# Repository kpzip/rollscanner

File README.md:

# rollscanner
88-Note Piano Roll scanner

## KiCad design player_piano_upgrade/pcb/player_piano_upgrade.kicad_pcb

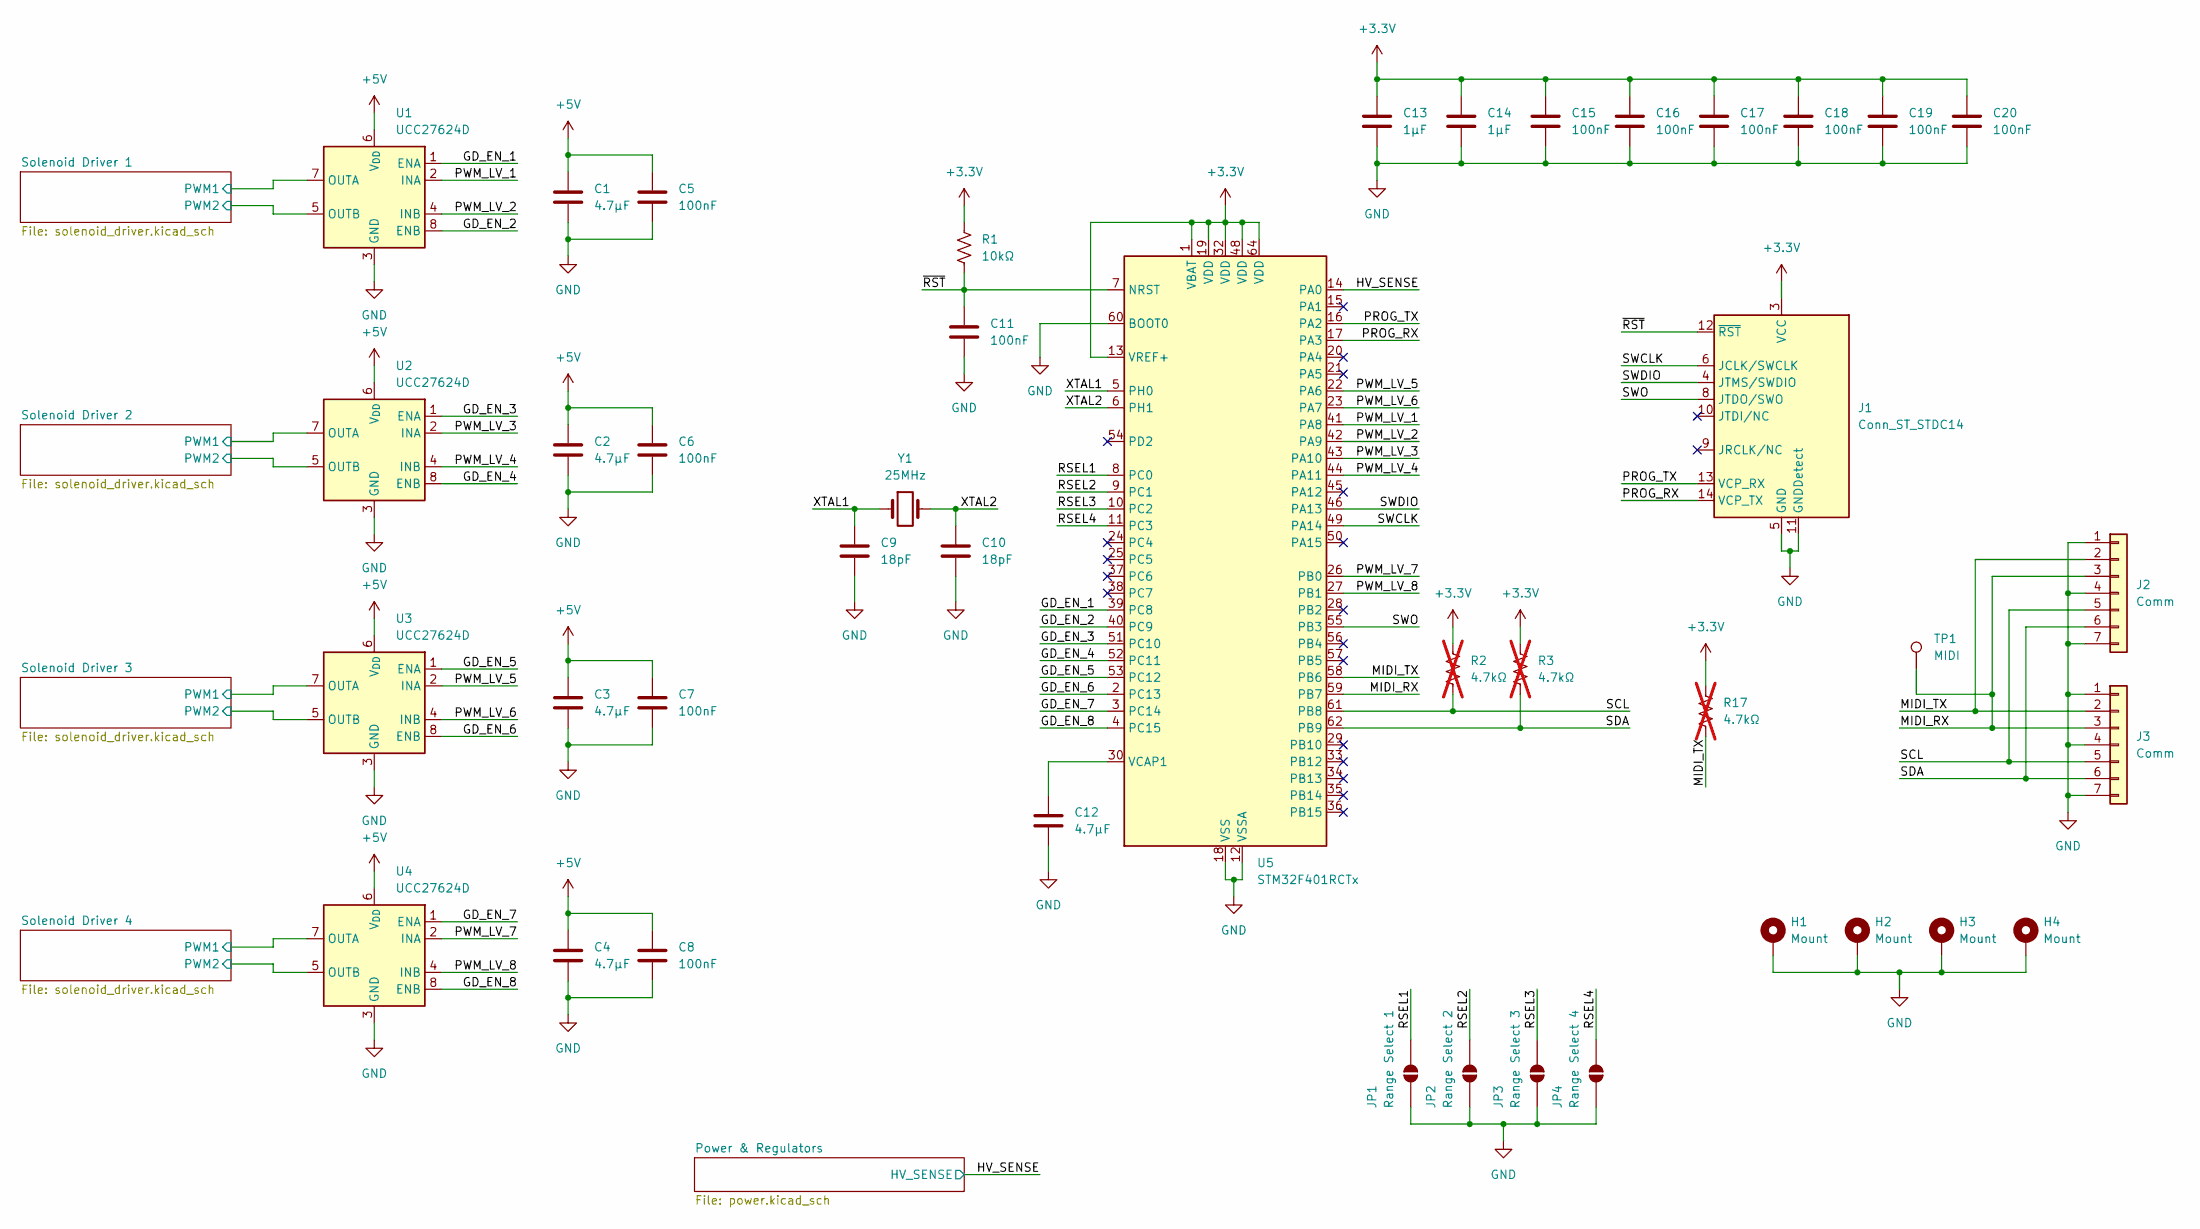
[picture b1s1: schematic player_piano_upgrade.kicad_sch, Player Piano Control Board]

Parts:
C1, C2, C3, C4, C12: 4.7μF; C_1206_3216Metric; Manufacturer Part Number CL31B475KAHNNNE
C5, C6, C7, C8, C11, C15, C16, C17, C18, C19, C20: 100nF; C_1206_3216Metric; Manufacturer Part Number CL31B104KBCNNNC
C9, C10: 18pF; C_0402_1005Metric; Manufacturer Part Number GJM1555C1H180GB01D
C13, C14: 1μF; C_1206_3216Metric; Manufacturer Part Number CL31B105KCHNNNE
H1, H2, H3, H4: Mount; MountingHole_3.2mm_M3_DIN965_Pad
J1: Conn_ST_STDC14; PinHeader_2x07_P1.27mm_Vertical_SMD; Manufacturer Part Number FTSH-107-01-L-DV-K
J2, J3: Comm; JST_PH_B7B-PH-K_1x07_P2.00mm_Vertical; Manufacturer Part Number B7B-PH-K-S
JP1: Range Select 1; SolderJumper-2_P1.3mm_Open_RoundedPad1.0x1.5mm
JP2: Range Select 2; SolderJumper-2_P1.3mm_Open_RoundedPad1.0x1.5mm
JP3: Range Select 3; SolderJumper-2_P1.3mm_Open_RoundedPad1.0x1.5mm
JP4: Range Select 4; SolderJumper-2_P1.3mm_Open_RoundedPad1.0x1.5mm
R1: 10kΩ; R_1206_3216Metric; Manufacturer Part Number FRC1206F1002TS
R2, R3, R17: 4.7kΩ; R_1206_3216Metric; Manufacturer Part Number FRC1206F4701TS; not fitted
TP1: MIDI; TestPoint_Pad_D1.0mm
U1, U2, U3, U4: UCC27624D; SOIC-8_3.9x4.9mm_P1.27mm; Manufacturer Part Number UCC27624DR
U5: STM32F401RCTx; LQFP-64_10x10mm_P0.5mm; Manufacturer Part Number STM32F401RCT6
Y1: 25MHz; Crystal_SMD_HC49-SD; Manufacturer Part Number ECS-250-18-5PX-F-TR

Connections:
+3.3V: C13.1, C14.1, C15.1, C16.1, C17.1, C18.1, C19.1, C20.1, J1.3 (VCC), R1.1, R2.1, R3.1, R17.1, U5.1 (VBAT), U5.13 (VREF+), U5.19 (VDD), U5.32 (VDD), U5.48 (VDD), U5.64 (VDD); also elsewhere on the board
+5V: C1.1, C2.1, C3.1, C4.1, C5.1, C6.1, C7.1, C8.1, U1.6 (V_{DD}), U2.6 (V_{DD}), U3.6 (V_{DD}), U4.6 (V_{DD}); also elsewhere on the board
/GD_EN_1: U1.1 (ENA), U5.39 (PC8)
/GD_EN_2: U1.8 (ENB), U5.40 (PC9)
/GD_EN_3: U2.1 (ENA), U5.51 (PC10)
/GD_EN_4: U2.8 (ENB), U5.52 (PC11)
/GD_EN_5: U3.1 (ENA), U5.53 (PC12)
/GD_EN_6: U3.8 (ENB), U5.2 (PC13)
/GD_EN_7: U4.1 (ENA), U5.3 (PC14)
/GD_EN_8: U4.8 (ENB), U5.4 (PC15)
/HV_SENSE: U5.14 (PA0); also elsewhere on the board
/MIDI_RX: J2.3, J3.3, TP1.1 (1_1), U5.59 (PB7)
/MIDI_TX: J2.2, J3.2, R17.2, U5.58 (PB6)
/PROG_RX: J1.14 (VCP_TX), U5.17 (PA3)
/PROG_TX: J1.13 (VCP_RX), U5.16 (PA2)
/PWM_LV_1: U1.2 (INA), U5.41 (PA8)
/PWM_LV_2: U1.4 (INB), U5.42 (PA9)
/PWM_LV_3: U2.2 (INA), U5.43 (PA10)
/PWM_LV_4: U2.4 (INB), U5.44 (PA11)
/PWM_LV_5: U3.2 (INA), U5.22 (PA6)
/PWM_LV_6: U3.4 (INB), U5.23 (PA7)
/PWM_LV_7: U4.2 (INA), U5.26 (PB0)
/PWM_LV_8: U4.4 (INB), U5.27 (PB1)
/RSEL1: JP1.2 (B), U5.8 (PC0)
/RSEL2: JP2.2 (B), U5.9 (PC1)
/RSEL3: JP3.2 (B), U5.10 (PC2)
/RSEL4: JP4.2 (B), U5.11 (PC3)
/SCL: J2.5, J3.5, R2.2, U5.61 (PB8)
/SDA: J2.6, J3.6, R3.2, U5.62 (PB9)
/SWCLK: J1.6 (JCLK/SWCLK), U5.49 (PA14)
/SWDIO: J1.4 (JTMS/SWDIO), U5.46 (PA13)
/SWO: J1.8 (JTDO/SWO), U5.55 (PB3)
/Solenoid Driver 1/PWM1: U1.7 (OUTA); also elsewhere on the board
/Solenoid Driver 1/PWM2: U1.5 (OUTB); also elsewhere on the board
/Solenoid Driver 2/PWM1: U2.7 (OUTA); also elsewhere on the board
/Solenoid Driver 2/PWM2: U2.5 (OUTB); also elsewhere on the board
/Solenoid Driver 3/PWM1: U3.7 (OUTA); also elsewhere on the board
/Solenoid Driver 3/PWM2: U3.5 (OUTB); also elsewhere on the board
/Solenoid Driver 4/PWM1: U4.7 (OUTA); also elsewhere on the board
/Solenoid Driver 4/PWM2: U4.5 (OUTB); also elsewhere on the board
/XTAL1: C9.1, U5.5 (PH0), Y1.1
/XTAL2: C10.1, U5.6 (PH1), Y1.2
/~RST: C11.1, J1.12 (~RST), R1.2, U5.7 (NRST)
GND: C1.2, C2.2, C3.2, C4.2, C5.2, C6.2, C7.2, C8.2, C9.2, C10.2, C11.2, C12.2, C13.2, C14.2, C15.2, C16.2, C17.2, C18.2, C19.2, C20.2, H1.1 (1_1), H2.1 (1_1), H3.1 (1_1), H4.1 (1_1), J1.5 (GND), J1.7 (GND), J1.11 (GNDDetect), J2.1, J2.4, J2.7, J3.1, J3.4, J3.7, JP1.1 (A), JP2.1 (A), JP3.1 (A), JP4.1 (A), U1.3 (GND), U2.3 (GND), U3.3 (GND), U4.3 (GND), U5.12 (VSSA), U5.18 (VSS), U5.31 (VSS), U5.47 (VSS), U5.60 (BOOT0), U5.63 (VSS); also elsewhere on the board
unnamed: C12.1, U5.30 (VCAP1)

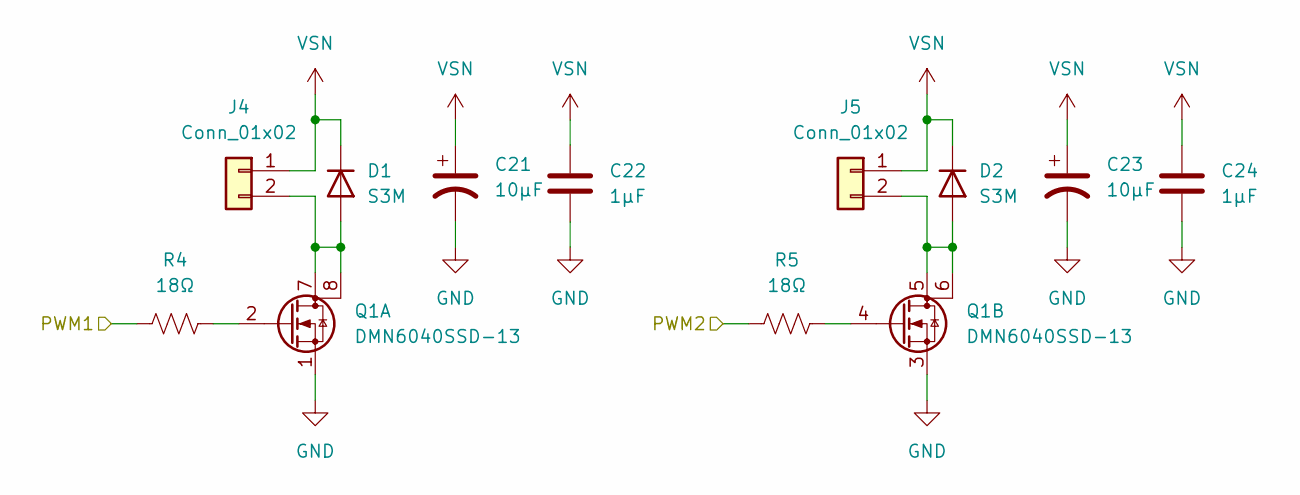
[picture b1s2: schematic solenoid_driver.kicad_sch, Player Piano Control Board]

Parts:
C21, C23: 10μF; CP_Elec_6.3x5.8; Manufacturer Part Number HBW100M1JTR-0606
C22, C24: 1μF; C_1206_3216Metric; Manufacturer Part Number CL31B105KCHNNNE
D1, D2: S3M; D_SMB; Manufacturer Part Number S3M
J4, J5: Conn_01x02; Molex_KK-254_AE-6410-02A_1x02_P2.54mm_Vertical; Manufacturer Part Number A2543WV-2P
Q1: DMN6040SSD-13; SOIC-8_3.9x4.9mm_P1.27mm; Manufacturer Part Number DMN6040SSD-13
R4, R5: 18Ω; R_1206_3216Metric; Manufacturer Part Number FRC1206F18R0TS

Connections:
/Solenoid Driver 1/PWM1: R4.1; also elsewhere on the board
/Solenoid Driver 1/PWM2: R5.1; also elsewhere on the board
GND: C21.2, C22.2, C23.2, C24.2, Q1.1 (S), Q1.3 (S); also elsewhere on the board
unnamed: D1.2 (A), J4.2, Q1.7 (D), Q1.8 (D)
unnamed: D2.2 (A), J5.2, Q1.5 (D), Q1.6 (D)
unnamed: Q1.2 (G), R4.2
unnamed: Q1.4 (G), R5.2
VSN: C21.1, C22.1, C23.1, C24.1, D1.1 (K), D2.1 (K), J4.1, J5.1; also elsewhere on the board

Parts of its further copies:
C25, C27, C29, C31, C33, C35: 10μF; CP_Elec_6.3x5.8; Manufacturer Part Number HBW100M1JTR-0606
C26, C28, C30, C32, C34, C36: 1μF; C_1206_3216Metric; Manufacturer Part Number CL31B105KCHNNNE
D3, D4, D5, D6, D7, D8: S3M; D_SMB; Manufacturer Part Number S3M
J6, J7, J8, J9, J10, J11: Conn_01x02; Molex_KK-254_AE-6410-02A_1x02_P2.54mm_Vertical; Manufacturer Part Number A2543WV-2P
Q2, Q3, Q4: DMN6040SSD-13; SOIC-8_3.9x4.9mm_P1.27mm; Manufacturer Part Number DMN6040SSD-13
R6, R7, R8, R9, R10, R11: 18Ω; R_1206_3216Metric; Manufacturer Part Number FRC1206F18R0TS

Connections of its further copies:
/Solenoid Driver 2/PWM1: R6.1; also elsewhere on the board
/Solenoid Driver 2/PWM2: R7.1; also elsewhere on the board
/Solenoid Driver 3/PWM1: R8.1; also elsewhere on the board
/Solenoid Driver 3/PWM2: R9.1; also elsewhere on the board
/Solenoid Driver 4/PWM1: R10.1; also elsewhere on the board
/Solenoid Driver 4/PWM2: R11.1; also elsewhere on the board
GND: C25.2, C26.2, C27.2, C28.2, C29.2, C30.2, C31.2, C32.2, C33.2, C34.2, C35.2, C36.2, Q2.1 (S), Q2.3 (S), Q3.1 (S), Q3.3 (S), Q4.1 (S), Q4.3 (S); also elsewhere on the board
unnamed: D3.2 (A), J6.2, Q2.7 (D), Q2.8 (D)
unnamed: D4.2 (A), J7.2, Q2.5 (D), Q2.6 (D)
unnamed: D5.2 (A), J8.2, Q3.7 (D), Q3.8 (D)
unnamed: D6.2 (A), J9.2, Q3.5 (D), Q3.6 (D)
unnamed: D7.2 (A), J10.2, Q4.7 (D), Q4.8 (D)
unnamed: D8.2 (A), J11.2, Q4.5 (D), Q4.6 (D)
unnamed: Q2.2 (G), R6.2
unnamed: Q2.4 (G), R7.2
unnamed: Q3.2 (G), R8.2
unnamed: Q3.4 (G), R9.2
unnamed: Q4.2 (G), R10.2
unnamed: Q4.4 (G), R11.2
VSN: C25.1, C26.1, C27.1, C28.1, C29.1, C30.1, C31.1, C32.1, C33.1, C34.1, C35.1, C36.1, D3.1 (K), D4.1 (K), D5.1 (K), D6.1 (K), D7.1 (K), D8.1 (K), J6.1, J7.1, J8.1, J9.1, J10.1, J11.1; also elsewhere on the board

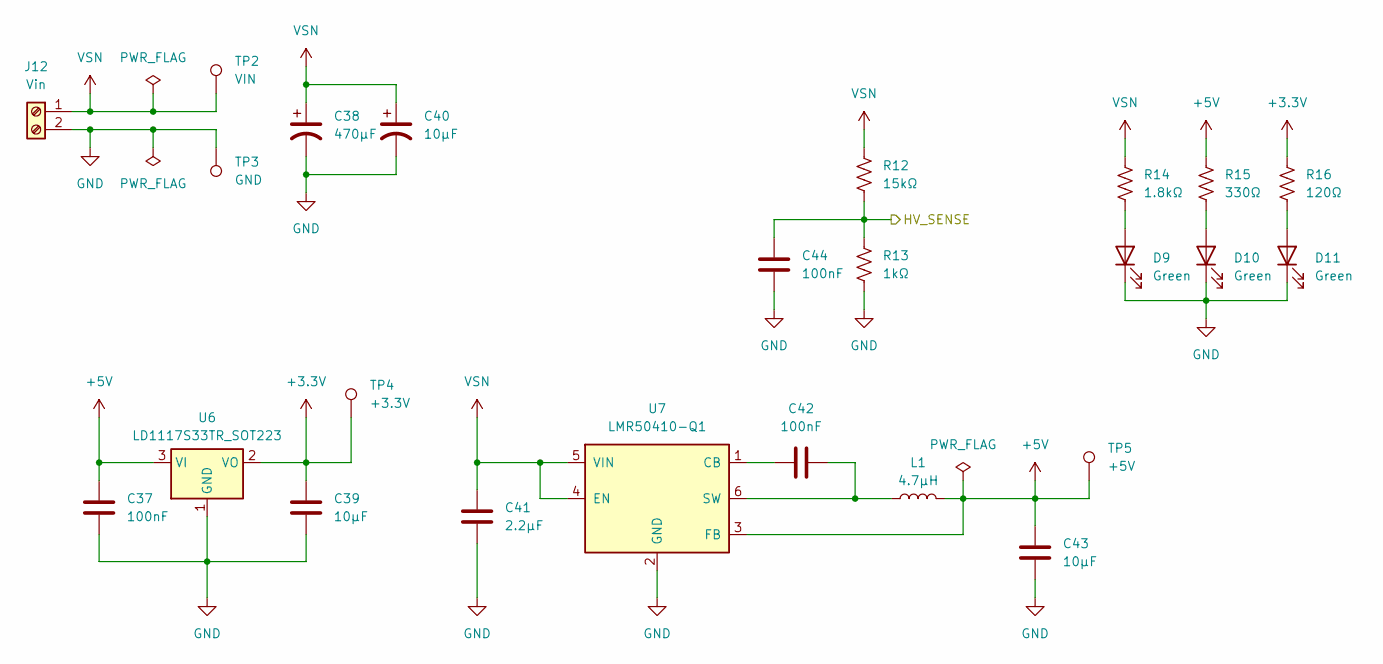
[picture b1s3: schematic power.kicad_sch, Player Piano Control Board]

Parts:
C37, C42, C44: 100nF; C_1206_3216Metric; Manufacturer Part Number CL31B104KBCNNNC
C38: 470μF; CP_Radial_D10.0mm_P5.00mm; Manufacturer Part Number 50PX470MEFC10X20
C39, C43: 10μF; C_1206_3216Metric; Manufacturer Part Number CL31A106MAHNNNE
C40: 10μF; CP_Elec_6.3x5.8; Manufacturer Part Number HBW100M1JTR-0606
C41: 2.2μF; C_1206_3216Metric; Manufacturer Part Number TCC1206X7R225K101HT
D9, D10, D11: Green; LED_D5.0mm; Manufacturer Part Number WP7113GD
J12: Vin; TerminalBlock_CUI_TB007-508-02_1x02_P5.08mm_Horizontal; Manufacturer Part Number WJ500V-5.08-2P
L1: 4.7μH; L_1008_2520Metric_Pad1.43x2.20mm_HandSolder; Manufacturer Part Number DFE252012P-4R7M=P2
R12: 15kΩ; R_1206_3216Metric; Manufacturer Part Number HRC1206F1502HNTN
R13: 1kΩ; R_1206_3216Metric; Manufacturer Part Number FRC1206J102 TS
R14: 1.8kΩ; R_1206_3216Metric; Manufacturer Part Number AC1206FR-7W1K8L
R15: 330Ω; R_1206_3216Metric; Manufacturer Part Number RMS12FT3300
R16: 120Ω; R_1206_3216Metric; Manufacturer Part Number FRC1206F1200TS
TP2: VIN; TestPoint_Pad_D1.0mm
TP3: GND; TestPoint_Pad_D2.0mm
TP4: +3.3V; TestPoint_Pad_D1.0mm
TP5: +5V; TestPoint_Pad_D1.0mm
U6: LD1117S33TR_SOT223; SOT-223-3_TabPin2; Manufacturer Part Number LD1117S33TR
U7: LMR50410-Q1; SOT-23-6; Manufacturer Part Number LMR50410Y5FQDBVRQ1

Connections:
+3.3V: C39.1, R16.1, TP4.1 (1_1), U6.2 (VO); also elsewhere on the board
+5V: C37.1, C43.1, L1.2, R15.1, TP5.1 (1_1), U6.3 (VI), U7.3 (FB); also elsewhere on the board
/HV_SENSE: C44.2, R12.2, R13.1; also elsewhere on the board
GND: C37.2, C38.2, C39.2, C40.2, C41.2, C43.2, C44.1, D9.1 (K), D10.1 (K), D11.1 (K), J12.2, R13.2, TP3.1 (1_1), U6.1 (GND), U7.2 (GND); also elsewhere on the board
unnamed: D9.2 (A), R14.2
unnamed: D10.2 (A), R15.2
unnamed: D11.2 (A), R16.2
unnamed: C42.1, U7.1 (CB)
unnamed: C42.2, L1.1, U7.6 (SW)
VSN: C38.1, C40.1, C41.1, J12.1, R12.1, R14.1, TP2.1 (1_1), U7.4 (EN), U7.5 (VIN); also elsewhere on the board

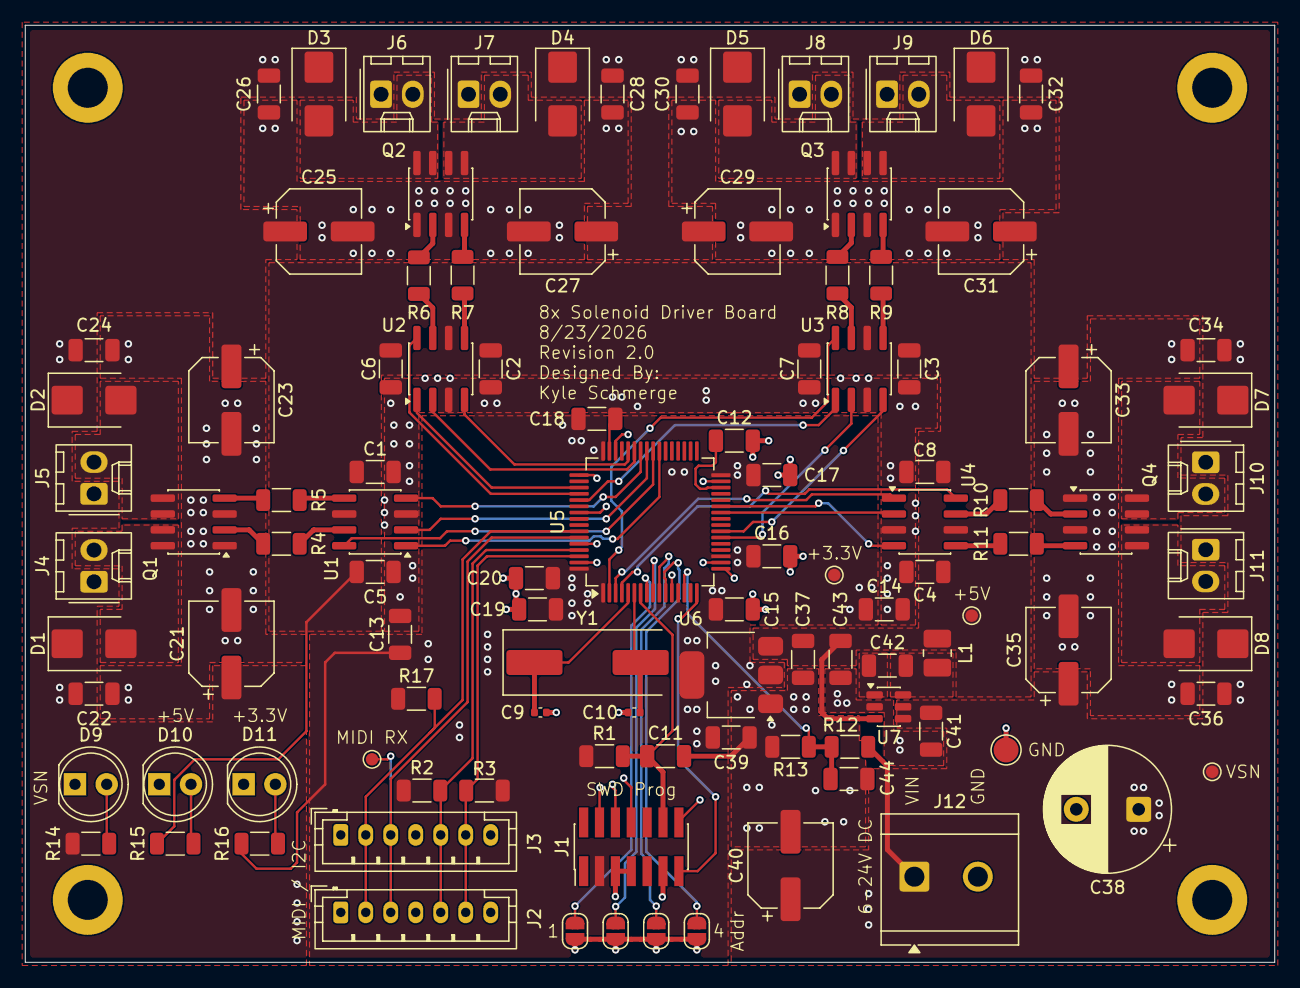
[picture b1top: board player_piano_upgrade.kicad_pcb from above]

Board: 4 copper layers, 100.0 x 75.0 mm, 110 parts (0 on the bottom side), 67 nets.

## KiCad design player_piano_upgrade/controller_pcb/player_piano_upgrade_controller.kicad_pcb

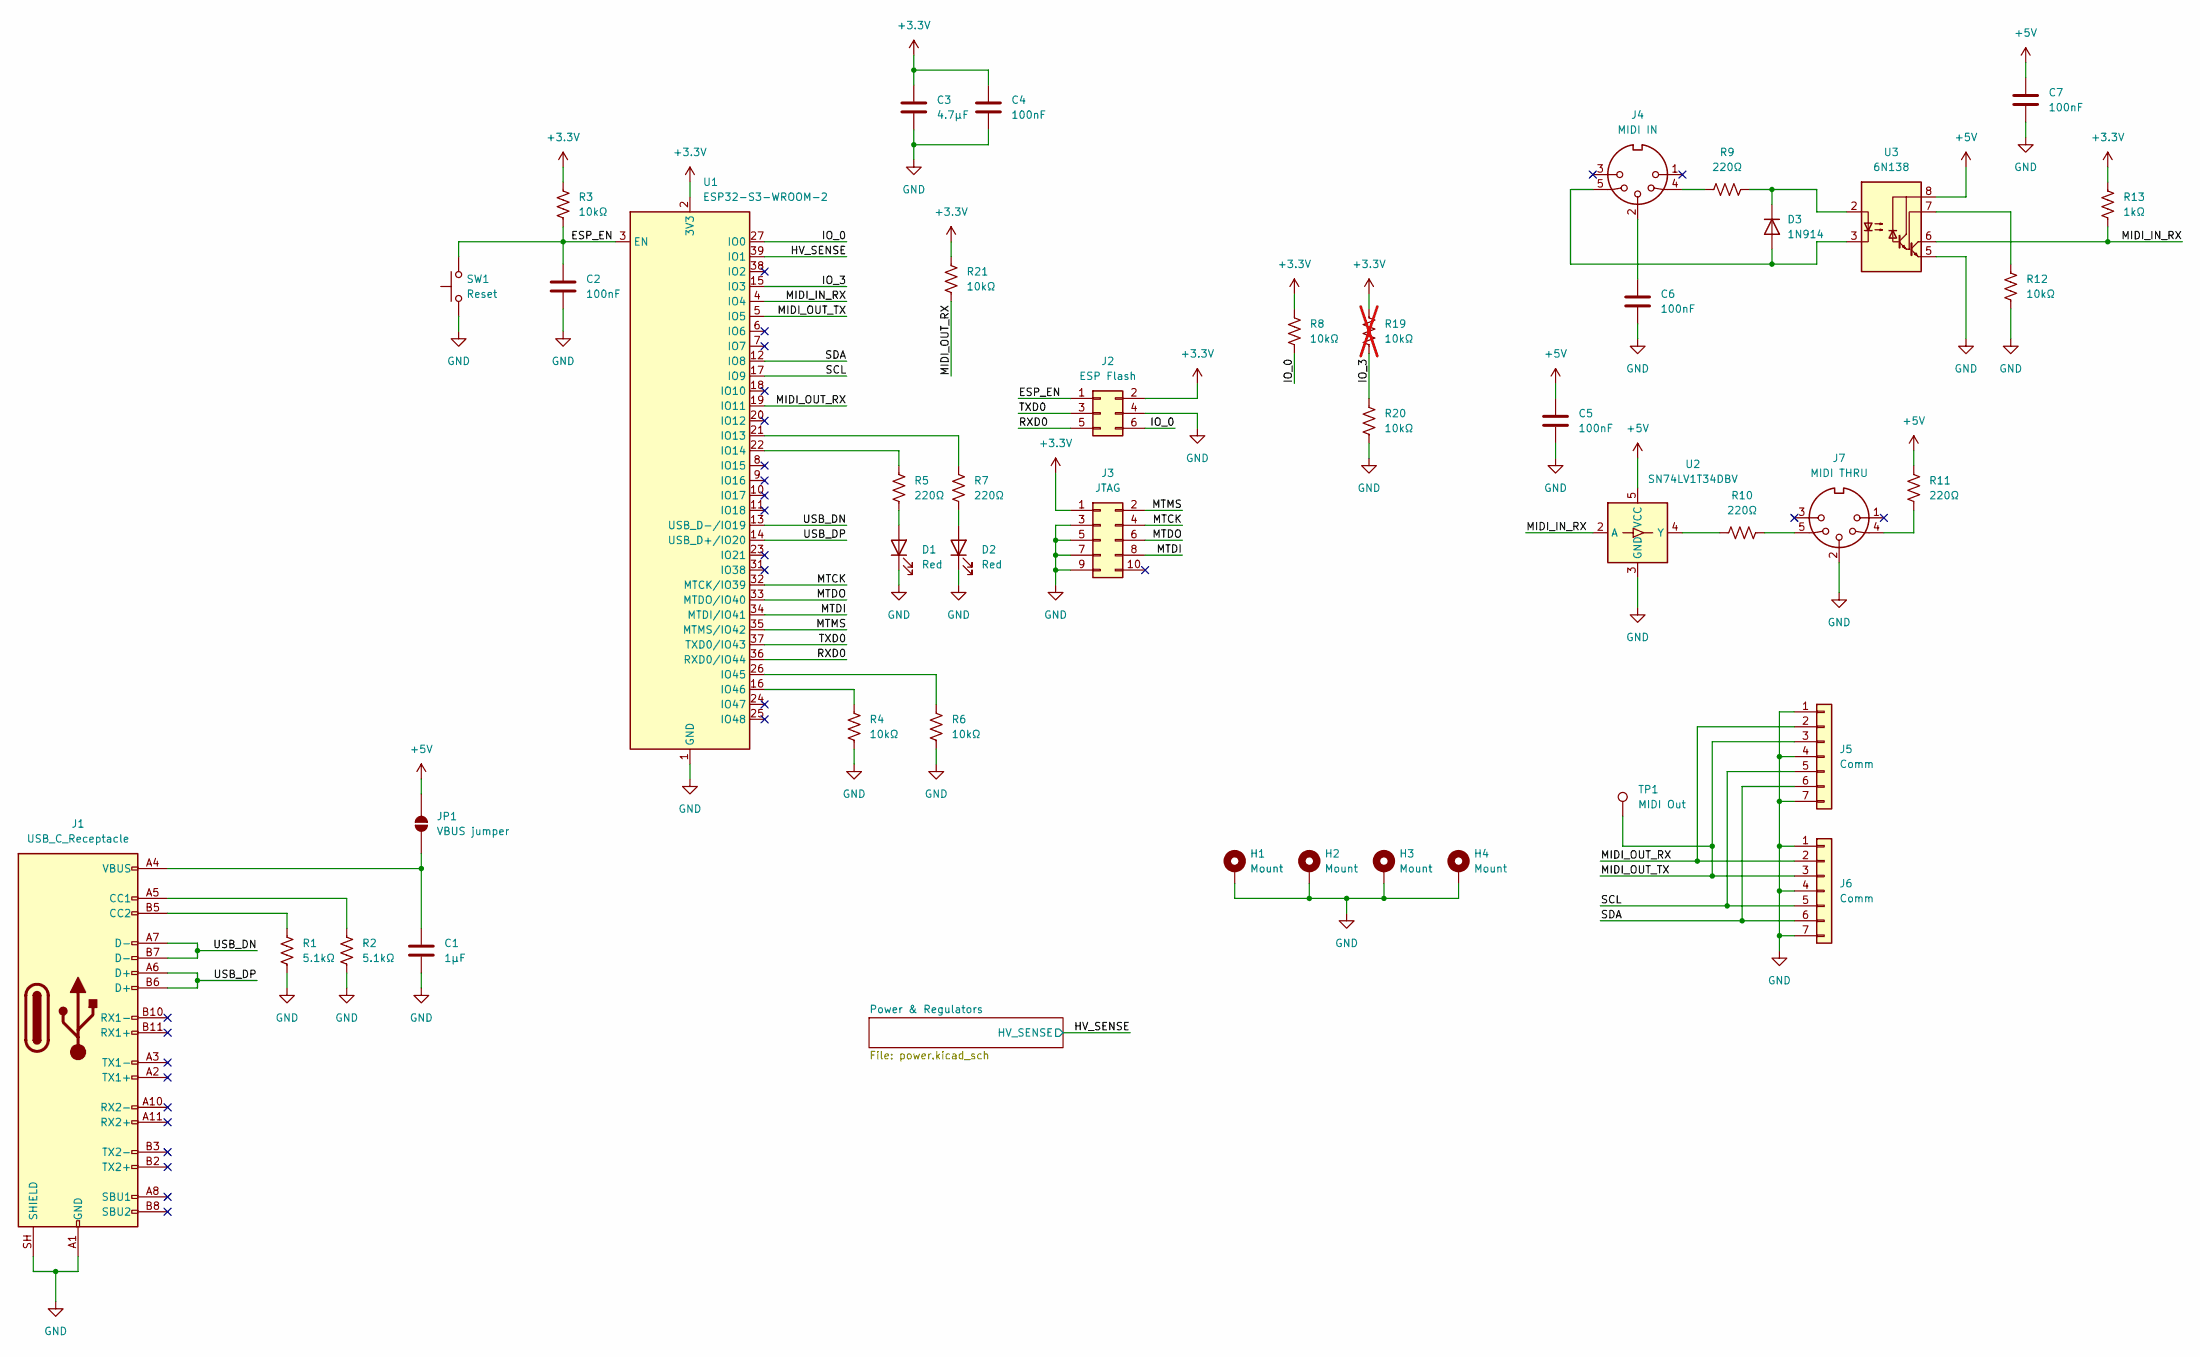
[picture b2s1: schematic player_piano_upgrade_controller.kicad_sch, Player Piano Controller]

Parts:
C1: 1μF; C_1206_3216Metric_Pad1.33x1.80mm_HandSolder; Manufacturer Part Number CL31B105KAHNNNE
C2, C4, C5, C6, C7: 100nF; C_1206_3216Metric_Pad1.33x1.80mm_HandSolder; Manufacturer Part Number 1206B104K500CT
C3: 4.7μF; C_1206_3216Metric_Pad1.33x1.80mm_HandSolder; Manufacturer Part Number CL31B475KAHNNNE
D1, D2: Red; LED_D5.0mm; Manufacturer Part Number XL-502SURD
D3: 1N914; D_SOD-523; Manufacturer Part Number 1N914BWT
H1, H2, H3, H4: Mount; MountingHole_3.2mm_M3_DIN965_Pad
J1: USB_C_Receptacle; USB_C_Receptacle_short; Manufacturer Part Number USB4056-03-A
J2: ESP Flash; IDC-Header_2x03_P2.54mm_Vertical; Manufacturer Part Number 61200621621
J3: JTAG; IDC-Header_2x05_P2.54mm_Vertical; Manufacturer Part Number IDC2.54-2*5PZ
J4: MIDI IN; KYCON_KCDX-5S-N; Manufacturer Part Number KCDX-5S-N
J5, J6: Comm; JST_PH_B7B-PH-K_1x07_P2.00mm_Vertical; Manufacturer Part Number B7B-PH-K-S
J7: MIDI THRU; KYCON_KCDX-5S-N; Manufacturer Part Number KCDX-5S-N
JP1: VBUS jumper; SolderJumper-2_P1.3mm_Open_RoundedPad1.0x1.5mm
R1, R2: 5.1kΩ; R_1206_3216Metric_Pad1.30x1.75mm_HandSolder; Manufacturer Part Number RC1206FR-075K1L
R3, R4, R6, R8, R12, R20, R21: 10kΩ; R_1206_3216Metric_Pad1.30x1.75mm_HandSolder; Manufacturer Part Number RMCF1206FT10K0
R5, R7, R9, R10, R11: 220Ω; R_1206_3216Metric_Pad1.30x1.75mm_HandSolder; Manufacturer Part Number RMCF1206FT220R
R13: 1kΩ; R_1206_3216Metric_Pad1.30x1.75mm_HandSolder; Manufacturer Part Number RC1206FR-071KL
R19: 10kΩ; R_1206_3216Metric_Pad1.30x1.75mm_HandSolder; Manufacturer Part Number RMCF1206FT10K0; not fitted
SW1: Reset; SW_PUSH_6mm; Manufacturer Part Number PTS645SL43-2 LFS
TP1: MIDI Out; TestPoint_Pad_D1.0mm
U1: ESP32-S3-WROOM-2; Manufacturer Part Number ESP32-S3-WROOM-2-N32R16V
U2: SN74LV1T34DBV; SOT-23-5; Manufacturer Part Number SN74LV1T34DBVR
U3: 6N138; SOIC-8_3.9x4.9mm_P1.27mm; Manufacturer Part Number HCPL-0701

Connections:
+3.3V: C3.1, C4.1, J2.2, J3.1, R3.1, R8.1, R13.1, R19.1, R21.1, U1.2 (3V3); also elsewhere on the board
+5V: C5.1, C7.1, JP1.2 (B), R11.2, U2.5 (VCC), U3.8 (VCC); also elsewhere on the board
/ESP_EN: C2.1, J2.1, R3.2, SW1.2, U1.3 (EN)
/HV_SENSE: U1.39 (IO1); also elsewhere on the board
/IO_0: J2.6, R8.2, U1.27 (IO0)
/IO_3: R19.2, R20.1, U1.15 (IO3)
/MIDI_IN_RX: R13.2, U1.4 (IO4), U2.2 (A), U3.6 (VO2)
/MIDI_OUT_RX: J5.2, J6.2, R21.2, U1.19 (IO11)
/MIDI_OUT_TX: J5.3, J6.3, TP1.1 (1_1), U1.5 (IO5)
/MTCK: J3.4, U1.32 (MTCK/IO39)
/MTDI: J3.8, U1.34 (MTDI/IO41)
/MTDO: J3.6, U1.33 (MTDO/IO40)
/MTMS: J3.2, U1.35 (MTMS/IO42)
/RXD0: J2.5, U1.36 (RXD0/IO44)
/SCL: J5.5, J6.5, U1.17 (IO9)
/SDA: J5.6, J6.6, U1.12 (IO8)
/TXD0: J2.3, U1.37 (TXD0/IO43)
/USB_DN: J1.A7 (D-), J1.B7 (D-), U1.13 (USB_D-/IO19)
/USB_DP: J1.A6 (D+), J1.B6 (D+), U1.14 (USB_D+/IO20)
GND: C1.2, C2.2, C3.2, C4.2, C5.2, C6.2, C7.2, D1.1 (K), D2.1 (K), H1.1 (1_1), H2.1 (1_1), H3.1 (1_1), H4.1 (1_1), J1.A1 (GND), J1.A12 (GND), J1.B1 (GND), J1.B12 (GND), J1.SH (SHIELD), J2.4, J3.3, J3.5, J3.7, J3.9, J5.1, J5.4, J5.7, J6.1, J6.4, J6.7, J7.2, R1.2, R2.2, R4.2, R6.2, R12.2, R20.2, SW1.1, U1.1 (GND), U1.40 (GND), U1.41 (GND), U2.3 (GND), U3.5 (GND); also elsewhere on the board
unnamed: C6.1, J4.2
unnamed: D1.2 (A), R5.1
unnamed: D2.2 (A), R7.1
unnamed: D3.2 (A), J4.5, U3.3 (C2)
unnamed: D3.1 (K), R9.2, U3.2 (C1)
unnamed: J1.A5 (CC1), R2.1
unnamed: J1.B5 (CC2), R1.1
unnamed: J4.4, R9.1
unnamed: J7.4, R11.1
unnamed: J7.5, R10.1
unnamed: C1.1, J1.A4 (VBUS), J1.A9 (VBUS), J1.B4 (VBUS), J1.B9 (VBUS), JP1.1 (A)
unnamed: R7.2, U1.21 (IO13)
unnamed: R5.2, U1.22 (IO14)
unnamed: R6.1, U1.26 (IO45)
unnamed: R4.1, U1.16 (IO46)
unnamed: R10.2, U2.4 (Y)
unnamed: R12.1, U3.7 (VO1)

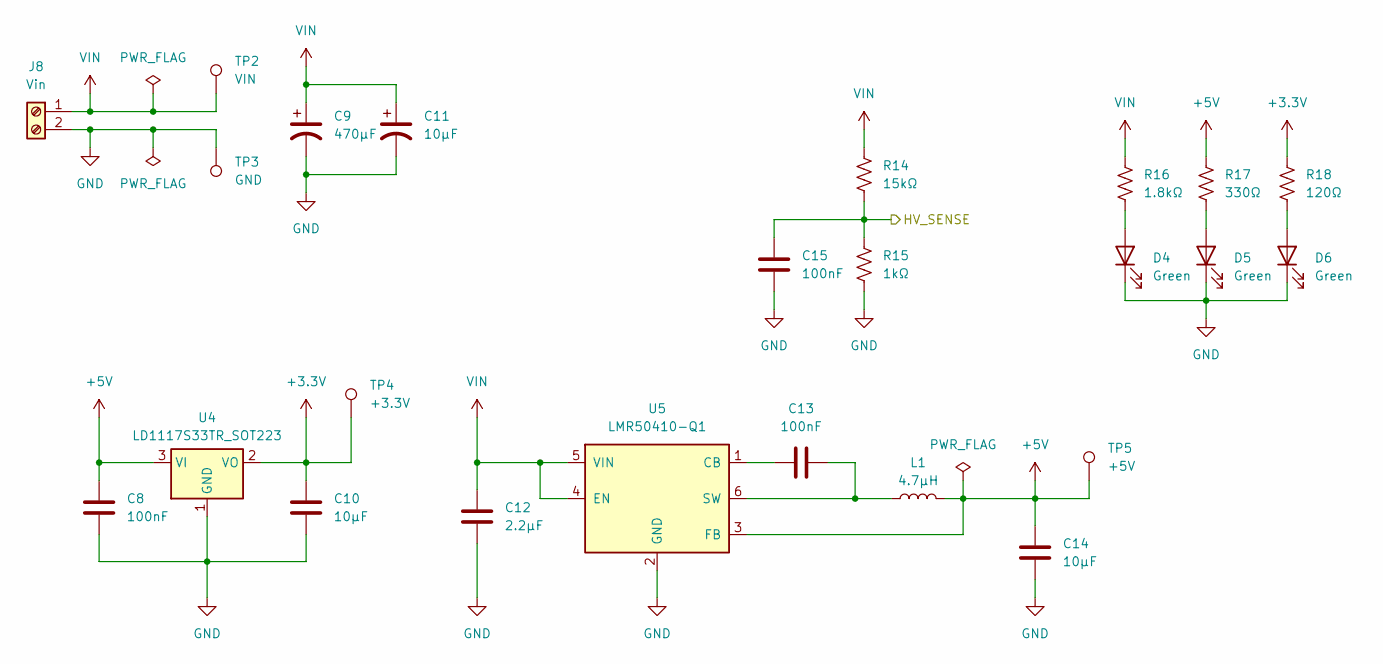
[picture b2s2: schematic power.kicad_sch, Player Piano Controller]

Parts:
C8, C13, C15: 100nF; C_1206_3216Metric; Manufacturer Part Number CL31B104KBCNNNC
C9: 470μF; CP_Radial_D10.0mm_P5.00mm; Manufacturer Part Number 50PX470MEFC10X20
C10, C14: 10μF; C_1206_3216Metric; Manufacturer Part Number CL31A106MAHNNNE
C11: 10μF; CP_Elec_6.3x5.8; Manufacturer Part Number HBW100M1JTR-0606
C12: 2.2μF; C_1206_3216Metric; Manufacturer Part Number TCC1206X7R225K101HT
D4, D5, D6: Green; LED_D5.0mm; Manufacturer Part Number WP7113GD
J8: Vin; TerminalBlock_CUI_TB007-508-02_1x02_P5.08mm_Horizontal; Manufacturer Part Number WJ500V-5.08-2P
L1: 4.7μH; L_1008_2520Metric_Pad1.43x2.20mm_HandSolder; Manufacturer Part Number DFE252012P-4R7M=P2
R14: 15kΩ; R_1206_3216Metric; Manufacturer Part Number HRC1206F1502HNTN
R15: 1kΩ; R_1206_3216Metric; Manufacturer Part Number FRC1206J102 TS
R16: 1.8kΩ; R_1206_3216Metric; Manufacturer Part Number AC1206FR-7W1K8L
R17: 330Ω; R_1206_3216Metric; Manufacturer Part Number RMS12FT3300
R18: 120Ω; R_1206_3216Metric; Manufacturer Part Number FRC1206F1200TS
TP2: VIN; TestPoint_Pad_D1.0mm
TP3: GND; TestPoint_Pad_D2.0mm
TP4: +3.3V; TestPoint_Pad_D1.0mm
TP5: +5V; TestPoint_Pad_D1.0mm
U4: LD1117S33TR_SOT223; SOT-223-3_TabPin2; Manufacturer Part Number LD1117S33TR
U5: LMR50410-Q1; SOT-23-6; Manufacturer Part Number LMR50410Y5FQDBVRQ1

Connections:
+3.3V: C10.1, R18.1, TP4.1 (1_1), U4.2 (VO); also elsewhere on the board
+5V: C8.1, C14.1, L1.2, R17.1, TP5.1 (1_1), U4.3 (VI), U5.3 (FB); also elsewhere on the board
/HV_SENSE: C15.2, R14.2, R15.1; also elsewhere on the board
GND: C8.2, C9.2, C10.2, C11.2, C12.2, C14.2, C15.1, D4.1 (K), D5.1 (K), D6.1 (K), J8.2, R15.2, TP3.1 (1_1), U4.1 (GND), U5.2 (GND); also elsewhere on the board
unnamed: D4.2 (A), R16.2
unnamed: D5.2 (A), R17.2
unnamed: D6.2 (A), R18.2
unnamed: C13.1, U5.1 (CB)
unnamed: C13.2, L1.1, U5.6 (SW)
VIN: C9.1, C11.1, C12.1, J8.1, R14.1, R16.1, TP2.1 (1_1), U5.4 (EN), U5.5 (VIN)

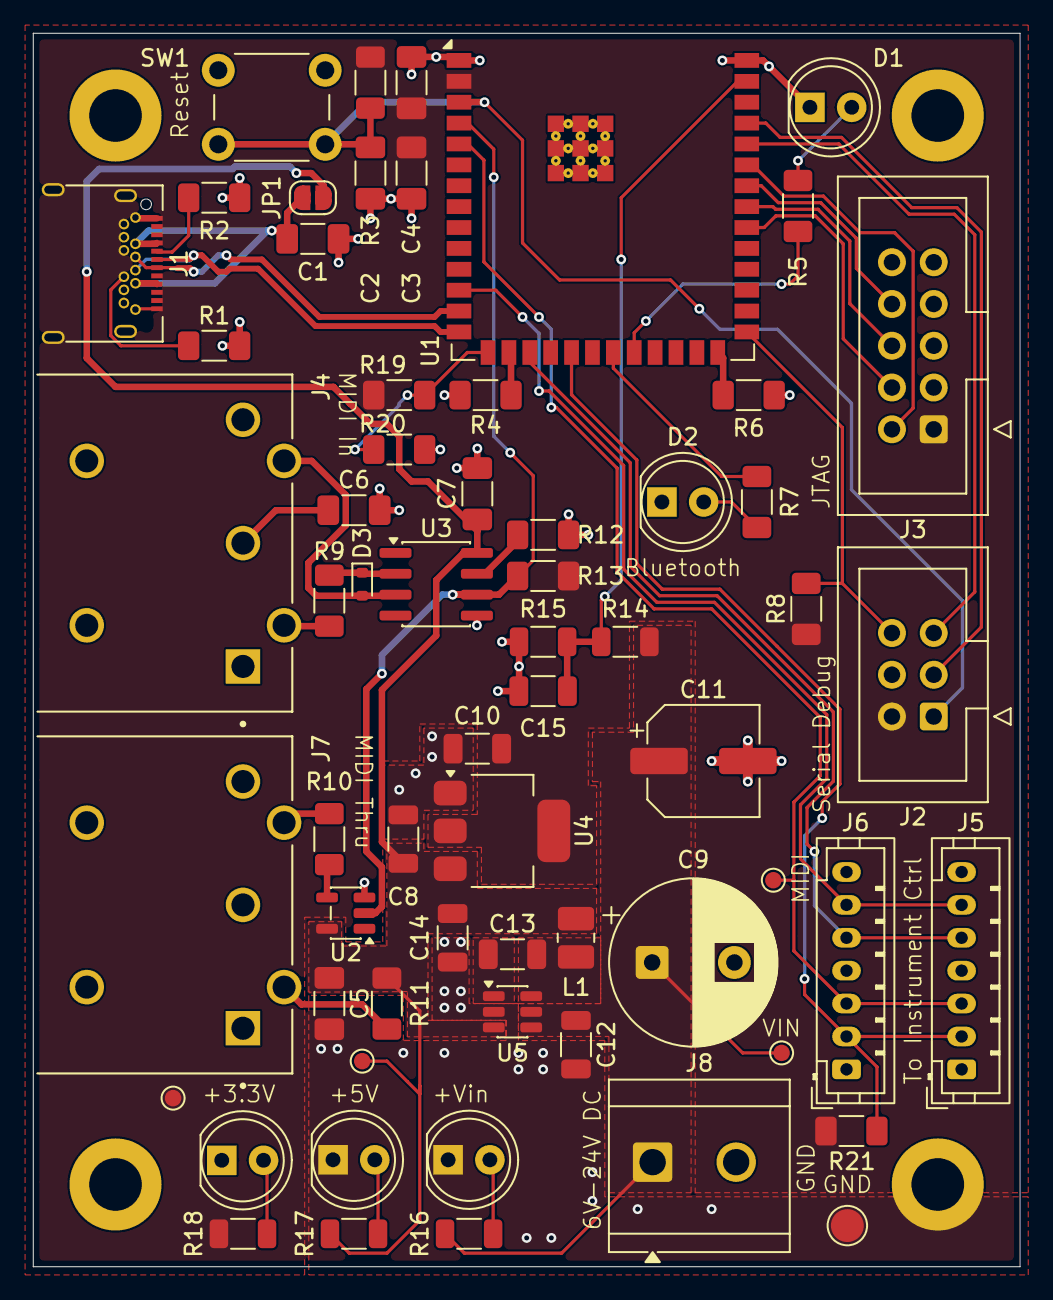
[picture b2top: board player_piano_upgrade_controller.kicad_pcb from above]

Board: 2 copper layers, 60.0 x 75.0 mm, 67 parts (0 on the bottom side), 43 nets.

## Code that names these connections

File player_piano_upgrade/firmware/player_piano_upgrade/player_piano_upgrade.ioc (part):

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Mcu.Name=STM32F401R(B-C)Tx
Mcu.Package=LQFP64
Mcu.UserName=STM32F401RCTx
PA0-WKUP.Signal=ADCx_IN0
PA10.Signal=S_TIM1_CH3
PA11.Signal=S_TIM1_CH4
PA2.Mode=Asynchronous
PA2.Signal=USART2_TX
PA3.Mode=Asynchronous
PA3.Signal=USART2_RX
PA6.Signal=S_TIM3_CH1
PA7.Signal=S_TIM3_CH2
PA8.Signal=S_TIM1_CH1
PA9.Signal=S_TIM1_CH2
PB0.Signal=S_TIM3_CH3
PB1.Signal=S_TIM3_CH4
PB6.GPIOParameters=GPIO_ModeDefaultPP
PB6.GPIO_ModeDefaultPP=GPIO_MODE_AF_OD
PB6.Mode=Asynchronous
PB6.Signal=USART1_TX
PB7.Mode=Asynchronous
PB7.Signal=USART1_RX
PB8.Mode=I2C
PB8.Signal=I2C1_SCL
PB9.Mode=I2C
PB9.Signal=I2C1_SDA
PC0.GPIOParameters=GPIO_PuPd,GPIO_Label
PC0.GPIO_Label=RSEL1
PC0.GPIO_PuPd=GPIO_PULLUP
PC0.Signal=GPIO_Input
PC1.GPIOParameters=GPIO_PuPd,GPIO_Label
PC1.GPIO_Label=RSEL2
PC1.GPIO_PuPd=GPIO_PULLUP
PC1.Signal=GPIO_Input
PC10.GPIOParameters=GPIO_Label
PC10.GPIO_Label=GD_EN_3
PC10.Signal=GPIO_Output
PC11.GPIOParameters=GPIO_Label
PC11.GPIO_Label=GD_EN_4
PC11.Signal=GPIO_Output
PC12.GPIOParameters=GPIO_Label
PC12.GPIO_Label=GD_EN_5
PC12.Signal=GPIO_Output
PC13-ANTI_TAMP.GPIOParameters=GPIO_Label
PC13-ANTI_TAMP.GPIO_Label=GD_EN_6
PC13-ANTI_TAMP.Signal=GPIO_Output
PC14-OSC32_IN.GPIOParameters=GPIO_Label
PC14-OSC32_IN.GPIO_Label=GD_EN_7
PC14-OSC32_IN.Signal=GPIO_Output
PC15-OSC32_OUT.GPIOParameters=GPIO_Label
PC15-OSC32_OUT.GPIO_Label=GD_EN_8
PC15-OSC32_OUT.Signal=GPIO_Output
PC2.GPIOParameters=GPIO_PuPd,GPIO_Label
PC2.GPIO_Label=RSEL3
PC2.GPIO_PuPd=GPIO_PULLUP
PC2.Signal=GPIO_Input
PC3.GPIOParameters=GPIO_PuPd,GPIO_Label
PC3.GPIO_Label=RSEL4
PC3.GPIO_PuPd=GPIO_PULLUP
PC3.Signal=GPIO_Input
PC8.GPIOParameters=GPIO_Label
PC8.GPIO_Label=GD_EN_1
PC8.Signal=GPIO_Output
PC9.GPIOParameters=GPIO_Label
PC9.GPIO_Label=GD_EN_2
PC9.Signal=GPIO_Output
PH0\ -\ OSC_IN.Mode=HSE-External-Oscillator
PH0\ -\ OSC_IN.Signal=RCC_OSC_IN
PH1\ -\ OSC_OUT.Mode=HSE-External-Oscillator
PH1\ -\ OSC_OUT.Signal=RCC_OSC_OUT
RCC.HSE_VALUE=25000000
RCC.SYSCLKFreq_VALUE=84000000
RCC.SYSCLKSource=RCC_SYSCLKSOURCE_PLLCLK
board=custom

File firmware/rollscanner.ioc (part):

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Mcu.Name=STM32G431R(6-8-B)Tx
Mcu.Package=LQFP64
Mcu.UserName=STM32G431RBTx
PA0.Signal=S_TIM2_CH1
PA10.Mode=Asynchronous
PA10.Signal=USART1_RX
PA11.Mode=Device
PA11.Signal=USB_DM
PA12.Mode=Device
PA12.Signal=USB_DP
PA13.Mode=JTAG_5_pins
PA13.Signal=SYS_JTMS-SWDIO
PA14.Mode=JTAG_5_pins
PA14.Signal=SYS_JTCK-SWCLK
PA15.Mode=JTAG_5_pins
PA15.Signal=SYS_JTDI
PA2.Mode=Asynchronous
PA2.Signal=USART2_TX
PA3.Mode=Asynchronous
PA3.Signal=USART2_RX
PA6.Signal=S_TIM3_CH1
PA8.Signal=S_TIM1_CH1
PA9.Mode=Asynchronous
PA9.Signal=USART1_TX
PB0.GPIOParameters=GPIO_Label
PB0.GPIO_Label=DIR_1
PB0.Signal=GPIO_Output
PB1.GPIOParameters=GPIO_Label
PB1.GPIO_Label=DIR_2
PB1.Signal=GPIO_Output
PB12.Mode=IN11-Single-Ended
PB12.Signal=ADC1_IN11
PB2.GPIOParameters=GPIO_Label
PB2.GPIO_Label=DIR_3
PB2.Signal=GPIO_Output
PB3.Mode=JTAG_5_pins
PB3.Signal=SYS_JTDO-SWO
PB4.Mode=JTAG_5_pins
PB4.Signal=SYS_JTRST
PB6.Signal=S_TIM4_CH1
PB7.Mode=I2C
PB7.Signal=I2C1_SDA
PB8-BOOT0.Mode=I2C
PB8-BOOT0.Signal=I2C1_SCL
PB9.Mode=Half_duplex(single_wire_mode)
PB9.Signal=USART3_TX
PC0.GPIOParameters=GPIO_Label
PC0.GPIO_Label=SEL_0
PC0.Signal=GPIO_Output
PC1.GPIOParameters=GPIO_Label
PC1.GPIO_Label=SEL_1
PC1.Signal=GPIO_Output
PC10.GPIOParameters=GPIO_Label
PC10.GPIO_Label=DIAG_3
PC10.Signal=GPXTI10
PC11.GPIOParameters=GPIO_Label
PC11.GPIO_Label=ENC_A
PC11.Signal=GPIO_Input
PC12.GPIOParameters=GPIO_Label
PC12.GPIO_Label=ENC_B
PC12.Signal=GPIO_Input
PC13.GPIOParameters=GPIO_PuPd,GPIO_Label
PC13.GPIO_Label=ROT_SW
PC13.GPIO_PuPd=GPIO_PULLUP
PC13.Signal=GPIO_Input
PC14-OSC32_IN.Mode=LSE-External-Oscillator
PC14-OSC32_IN.Signal=RCC_OSC32_IN
PC15-OSC32_OUT.Mode=LSE-External-Oscillator
PC15-OSC32_OUT.Signal=RCC_OSC32_OUT
PC2.GPIOParameters=GPIO_Label
PC2.GPIO_Label=SEL_2
PC2.Signal=GPIO_Output
PC3.GPIOParameters=GPIO_Label
PC3.GPIO_Label=SEL_3
PC3.Signal=GPIO_Output
PC4.GPIOParameters=GPIO_Label
PC4.GPIO_Label=SEL_4
PC4.Signal=GPIO_Output
PC5.GPIOParameters=GPIO_Label
PC5.GPIO_Label=SEL_5
PC5.Signal=GPIO_Output
PC6.GPIOParameters=GPIO_Label
PC6.GPIO_Label=SEL_6
PC6.Signal=GPIO_Output
PC7.GPIOParameters=GPIO_Label
PC7.GPIO_Label=SEL_7
PC7.Signal=GPIO_Output
PC8.GPIOParameters=GPIO_Label
PC8.GPIO_Label=DIAG_1
PC8.Signal=GPXTI8
PC9.GPIOParameters=GPIO_Label
PC9.GPIO_Label=DIAG_2
PC9.Signal=GPXTI9
PF0-OSC_IN.Mode=HSE-External-Oscillator
PF0-OSC_IN.Signal=RCC_OSC_IN
PF1-OSC_OUT.Mode=HSE-External-Oscillator
PF1-OSC_OUT.Signal=RCC_OSC_OUT
RCC.HSE_VALUE=32000000
RCC.SYSCLKFreq_VALUE=170000000
RCC.SYSCLKSource=RCC_SYSCLKSOURCE_PLLCLK
board=custom

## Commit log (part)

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2025-09-29 sdfg
2026-02-16 firmware
